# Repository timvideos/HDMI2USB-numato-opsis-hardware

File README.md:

The <a href="http://hdmi2usb.tv/numato-opsis">Numato Opsis</a>, the first open hardware for the
<a href="http://hdmi2usb.tv">HDMI2USB firmware</a>,
<a href="https://numato.com/product/numato-opsis-fpga-based-open-video-platform">can now be ordered
From Numato Labs
</a>

## Opsis Board - A open source HDMI2USB board

The [Numato](http://numato.com) Opsis board is the first
[HDMI2USB](http://hdmi2usb.tv) production board developed in conjugation with
the [TimVideos.us](http://code.timvideos.us) project. 

It's features include;
 * 2 x HDMI input ports,
 * 2 x HDMI output ports,
 * DisplayPort input and output ports,
 * 128Mbit DDR3-1600 ram,
 * Gigabit Ethernet with MAC address EEPROM,
 * Micro SD card,
 * Cypress FX2 for USB device functionality,
 * ULPI for USB OTG functionality,
 * Quad speed SPI flash.

Sample code for the Opsis can be found at https://github.com/timvideos/HDMI2USB-numato-opsis-sample-code

## Editing

The design in this repository was made using [KiCad](http://www.kicad-pcb.org/)
version **2013-07-07 BZR 4022**
([the version in Ubuntu Trusty](http://packages.ubuntu.com/trusty/kicad)).

## License

Opsis Board by Numato Systems Pvt. Ltd

The Numato HDMI2USB board is licensed under a
Creative Commons Attribution-ShareAlike 4.0 International License.

You should have received a copy of the license along with this
work. If not, see <http://creativecommons.org/licenses/by-sa/4.0/>.

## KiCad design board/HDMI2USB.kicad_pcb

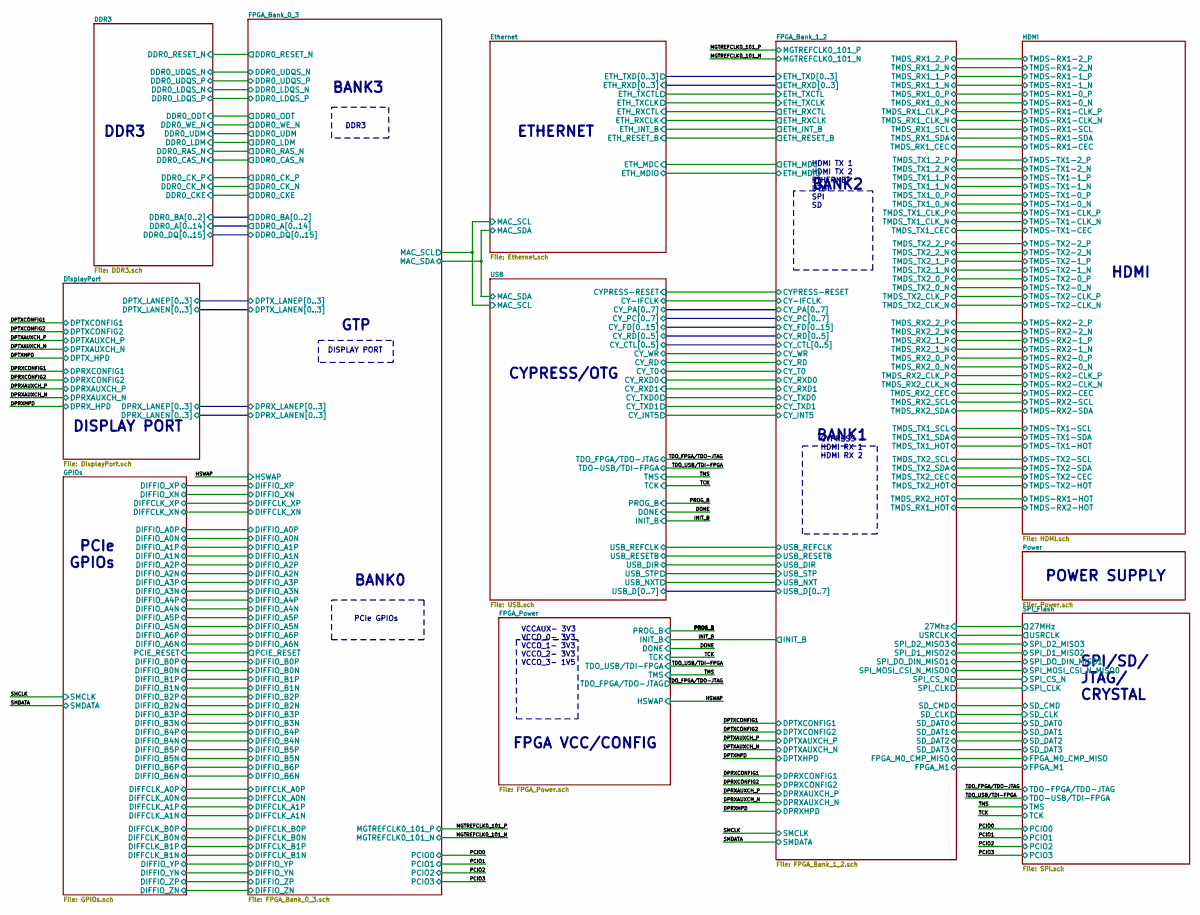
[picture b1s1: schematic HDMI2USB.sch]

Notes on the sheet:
HDMI
POWER SUPPLY
SPI/SD/ JTAG/ CRYSTAL
DISPLAY PORT
PCIe GPIOs
ETHERNET
CYPRESS/OTG
FPGA VCC/CONFIG
DDR3
BANK0
BANK3
BANK2
BANK1
PCIe GPIOs
GTP
CYPRESS HDMI RX 1 HDMI RX 2
HDMI TX 1 HDMI TX 2 ETHERNET UTMI SPI SD
VCCAUX- 3V3 VCCO_0- 3V3 VCCO_1- 3V3 VCCO_2- 3V3 VCCO_3- 1V5

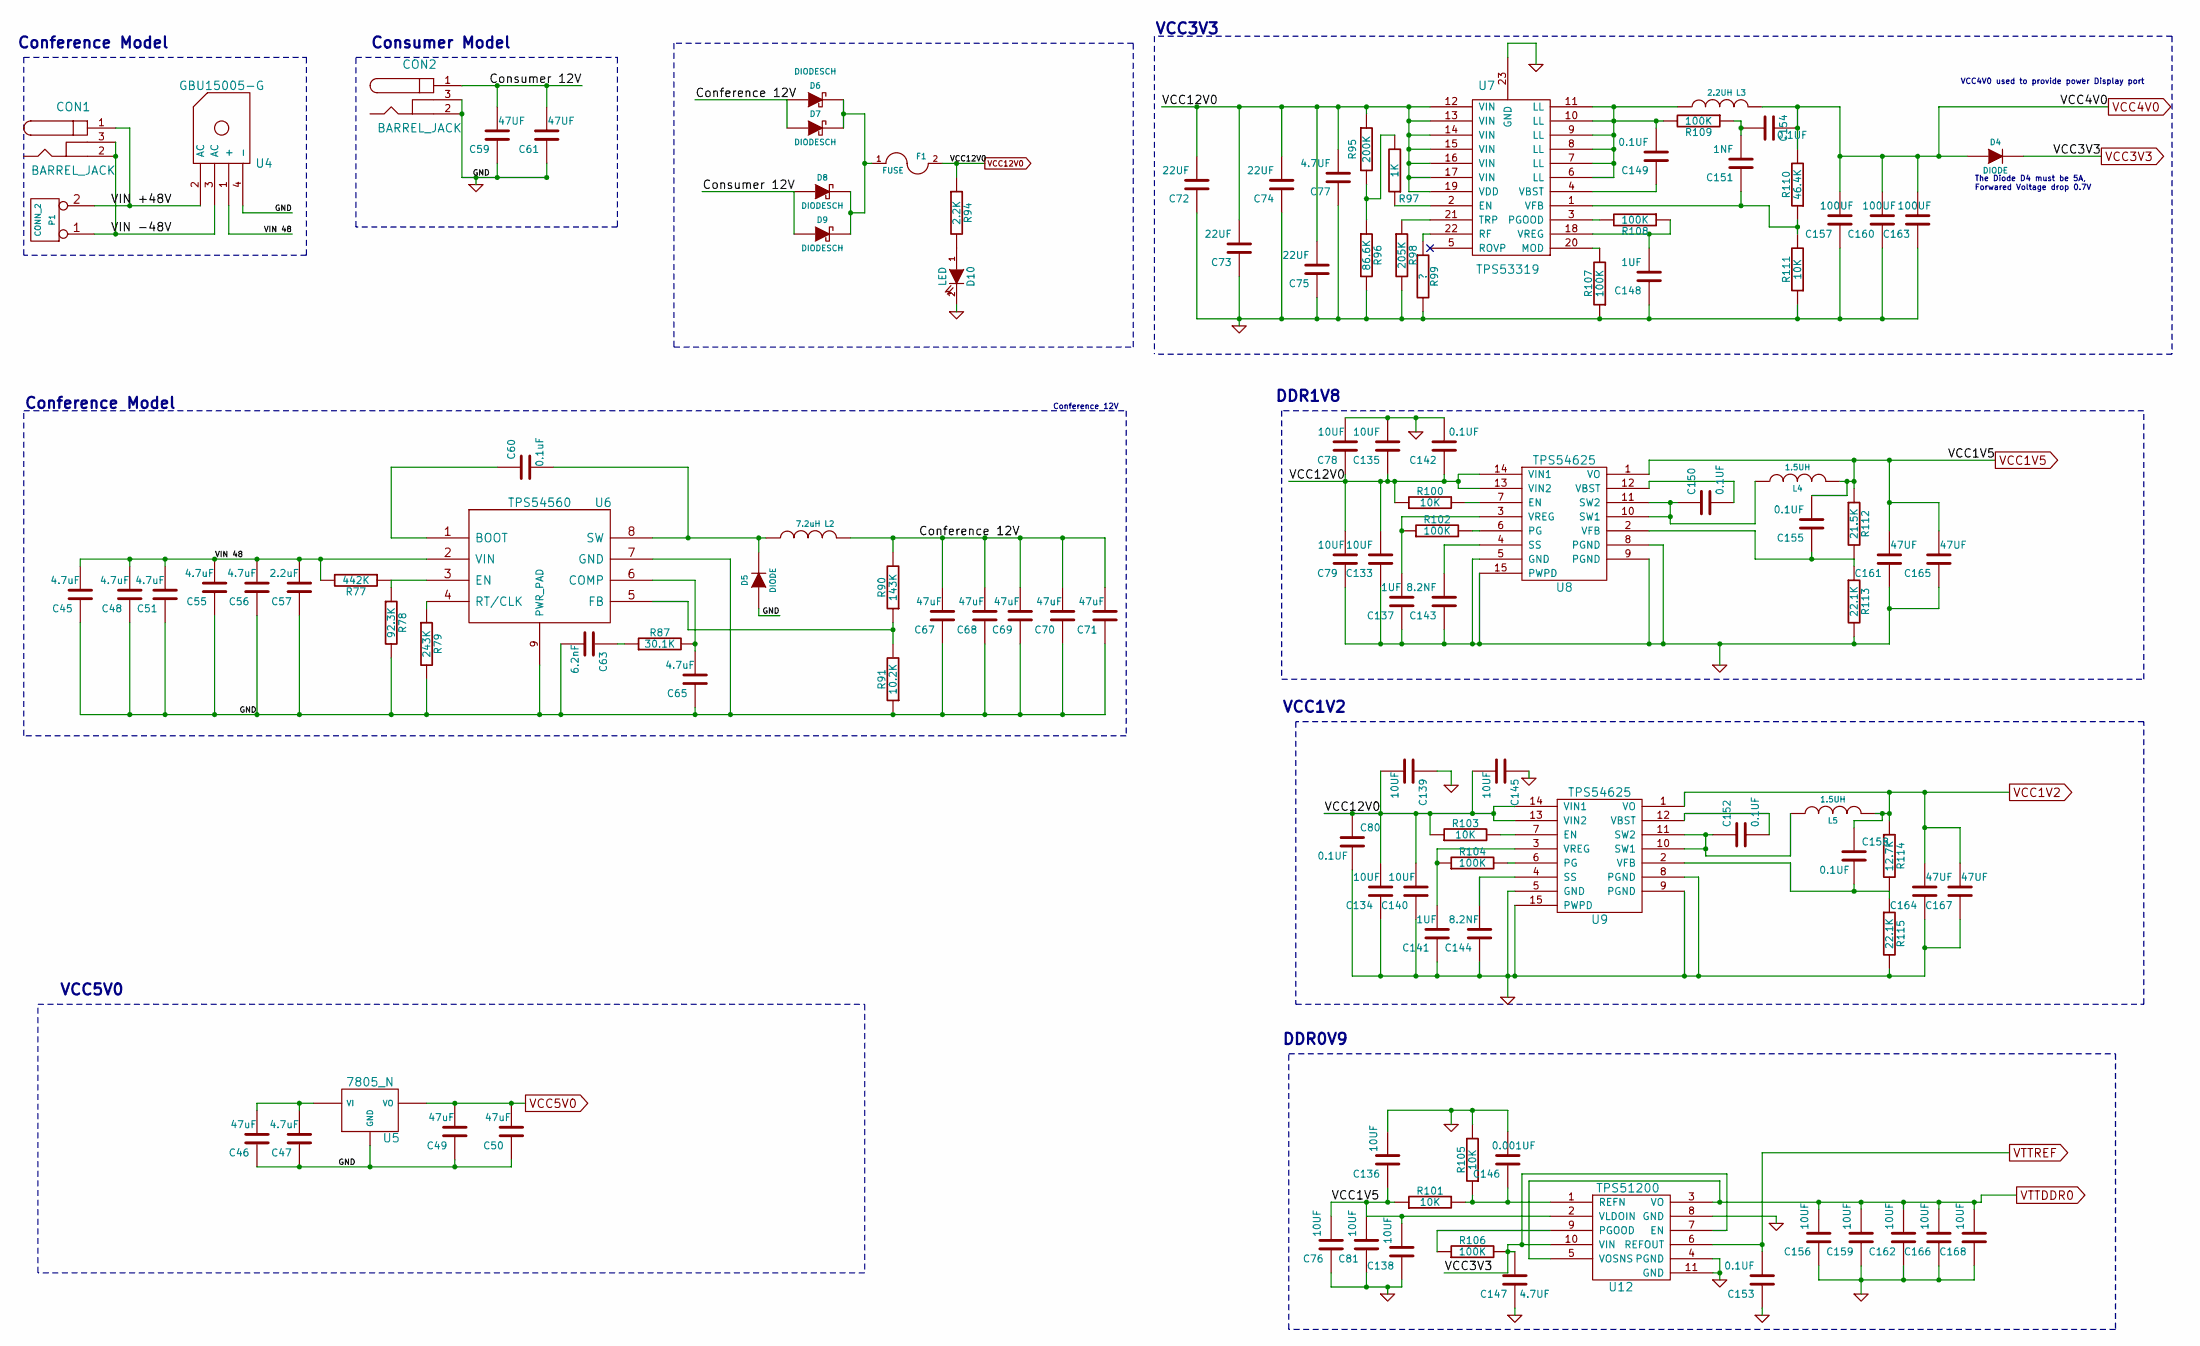
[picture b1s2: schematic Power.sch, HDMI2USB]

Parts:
C45, C47, C48, C51, C55, C56, C65: 4.7uF
C46, C49, C50, C67, C68, C69, C70, C71: 47uF
C57: 2.2uF
C59, C61, C161, C164, C165, C167: 47UF
C60: 0.1uF
C63: 6.2nF
C72, C73, C74, C75: 22UF
C76, C78, C79, C81, C133, C134, C135, C136, C138, C139, C140, C145, C156, C159, C162, C166, C168: 10UF
C77, C147: 4.7UF
C80, C142, C149, C150, C152, C153, C154, C155, C158: 0.1UF
C137, C141, C148: 1UF
C143, C144: 8.2NF
C146: 0.001UF
C151: 1NF
C157, C160, C163: 100UF
CON1, CON2: BARREL_JACK
D4, D5: DIODE
D6, D7, D8, D9: DIODESCH
D10: LED
F1: FUSE
L2: 7.2uH
L3: 2.2UH
L4, L5: 1.5UH
P1: CONN_2
R77: 442K
R78: 92.3K
R79: 243K
R87: 30.1K
R90: 143K
R91: 10.2K
R94: 2.2K
R95: 200K
R96: 86.6K
R97: 1K
R98: 205K
R99: ?
R100, R101, R103, R105, R111: 10K
R102, R104, R106, R107, R108, R109: 100K
R110: 46.4K
R112: 21.5K
R113, R115: 22.1K
R114: 12.7K
U4: GBU15005-G
U5: 7805_N
U6: TPS54560
U7: TPS53319
U8, U9: TPS54625
U12: TPS51200

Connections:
/Power/Conference 12V: C67.2, C68.2, C69.2, C70.2, C71.2, D6.1 (A), D7.1 (A), L2.2, R90.2
/Power/Consumer 12V: C59.2, C61.2, CON2.1, D8.1 (A), D9.1 (A)
/Power/VIN 48: C45.2, C48.2, C51.2, C55.2, C56.2, C57.2, R77.2, U4.1 (+), U6.2 (VIN)
/Power/VIN +48V: CON1.1, P1.2 (PM), U4.2 (AC)
/Power/VIN -48V: CON1.2, CON1.3, P1.1, U4.3 (AC)
unnamed: C65.2, R87.2, U6.6 (COMP)
unnamed: C63.1, R87.1
unnamed: C150.2, U8.12 (VBST)
unnamed: C150.1, L4.1, U8.10 (SW1), U8.11 (SW2)
unnamed: R79.1, U6.4 (RT/CLK)
unnamed: R77.1, R78.1, U6.3 (EN)
unnamed: C60.1, U6.1 (BOOT)
unnamed: C144.2, U9.4 (SS)
unnamed: R104.2, U9.6 (PG)
unnamed: C152.2, U9.12 (VBST)
unnamed: R103.2, U9.7 (EN)
unnamed: R102.2, U8.6 (PG)
unnamed: C143.2, U8.4 (SS)
unnamed: C152.1, L5.1, U9.10 (SW1), U9.11 (SW2)
unnamed: R100.2, U8.7 (EN)
unnamed: C149.1, U7.4 (VBST)
unnamed: C141.2, R104.1, U9.3 (VREG)
unnamed: R108.2, U7.3 (PGOOD)
unnamed: C148.2, R108.1, U7.18 (VREG)
unnamed: R107.2, U7.20 (MOD)
unnamed: R99.1, U7.22 (RF)
unnamed: R98.1, U7.21 (TRP)
unnamed: C137.2, R102.1, U8.3 (VREG)
unnamed: R97.1, U7.2 (EN)
unnamed: R106.1, U12.9 (PGOOD)
unnamed: R90.1, R91.2, U6.5 (FB)
unnamed: C60.2, D5.2 (K), L2.1, U6.8 (SW)
unnamed: C153.2, U12.6 (REFOUT)
unnamed: C158.2, R114.2, R115.1, U9.2 (VFB)
unnamed: C155.1, R112.2, R113.1, U8.2 (VFB)
unnamed: C46.2, C47.2, U5.1 (VI)
unnamed: D6.2 (K), D7.2 (K), D8.2 (K), D9.2 (K), F1.1
unnamed: C146.1, R101.2, R105.1, U12.1 (REFN)
unnamed: C151.1, R110.1, R111.2, U7.1 (VFB)
unnamed: C149.2, L3.1, R109.2, U7.6 (LL), U7.7 (LL), U7.8 (LL), U7.9 (LL), U7.10 (LL), U7.11 (LL)
unnamed: R95.2, R96.1, R97.2
unnamed: D10.1 (A), R94.2
VCC1V2: C158.1, C164.2, C167.2, L5.2, R114.1, U9.1 (VO); also elsewhere on the board
VCC1V5: C76.2, C81.2, C136.1, C138.2, C155.2, C161.2, C165.2, L4.2, R101.1, R112.1, U8.1 (VO), U12.2 (VLDOIN); also elsewhere on the board
VCC5V0: C49.2, C50.2, U5.3 (VO); also elsewhere on the board
VCC12V0: C72.2, C73.2, C74.2, C75.2, C77.2, C78.1, C79.2, C80.1, C133.2, C134.2, C135.1, C139.2, C140.2, C142.1, C145.2, F1.2, R94.1, R95.1, R100.1, R103.1, U7.12 (VIN), U7.13 (VIN), U7.14 (VIN), U7.15 (VIN), U7.16 (VIN), U7.17 (VIN), U7.19 (VDD), U8.13 (VIN2), U8.14 (VIN1), U9.13 (VIN2), U9.14 (VIN1); also elsewhere on the board
VTTDDR0: C156.2, C159.2, C162.2, C166.2, C168.2, U12.3 (VO), U12.5 (VOSNS); also elsewhere on the board

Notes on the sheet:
VCC3V3
DDR1V8
VCC1V2
DDR0V9
Consumer Model
Conference Model
Conference 12V
VCC5V0
VCC4V0 used to provide power Display port
The Diode D4 must be 5A, Forwared Voltage drop 0.7V

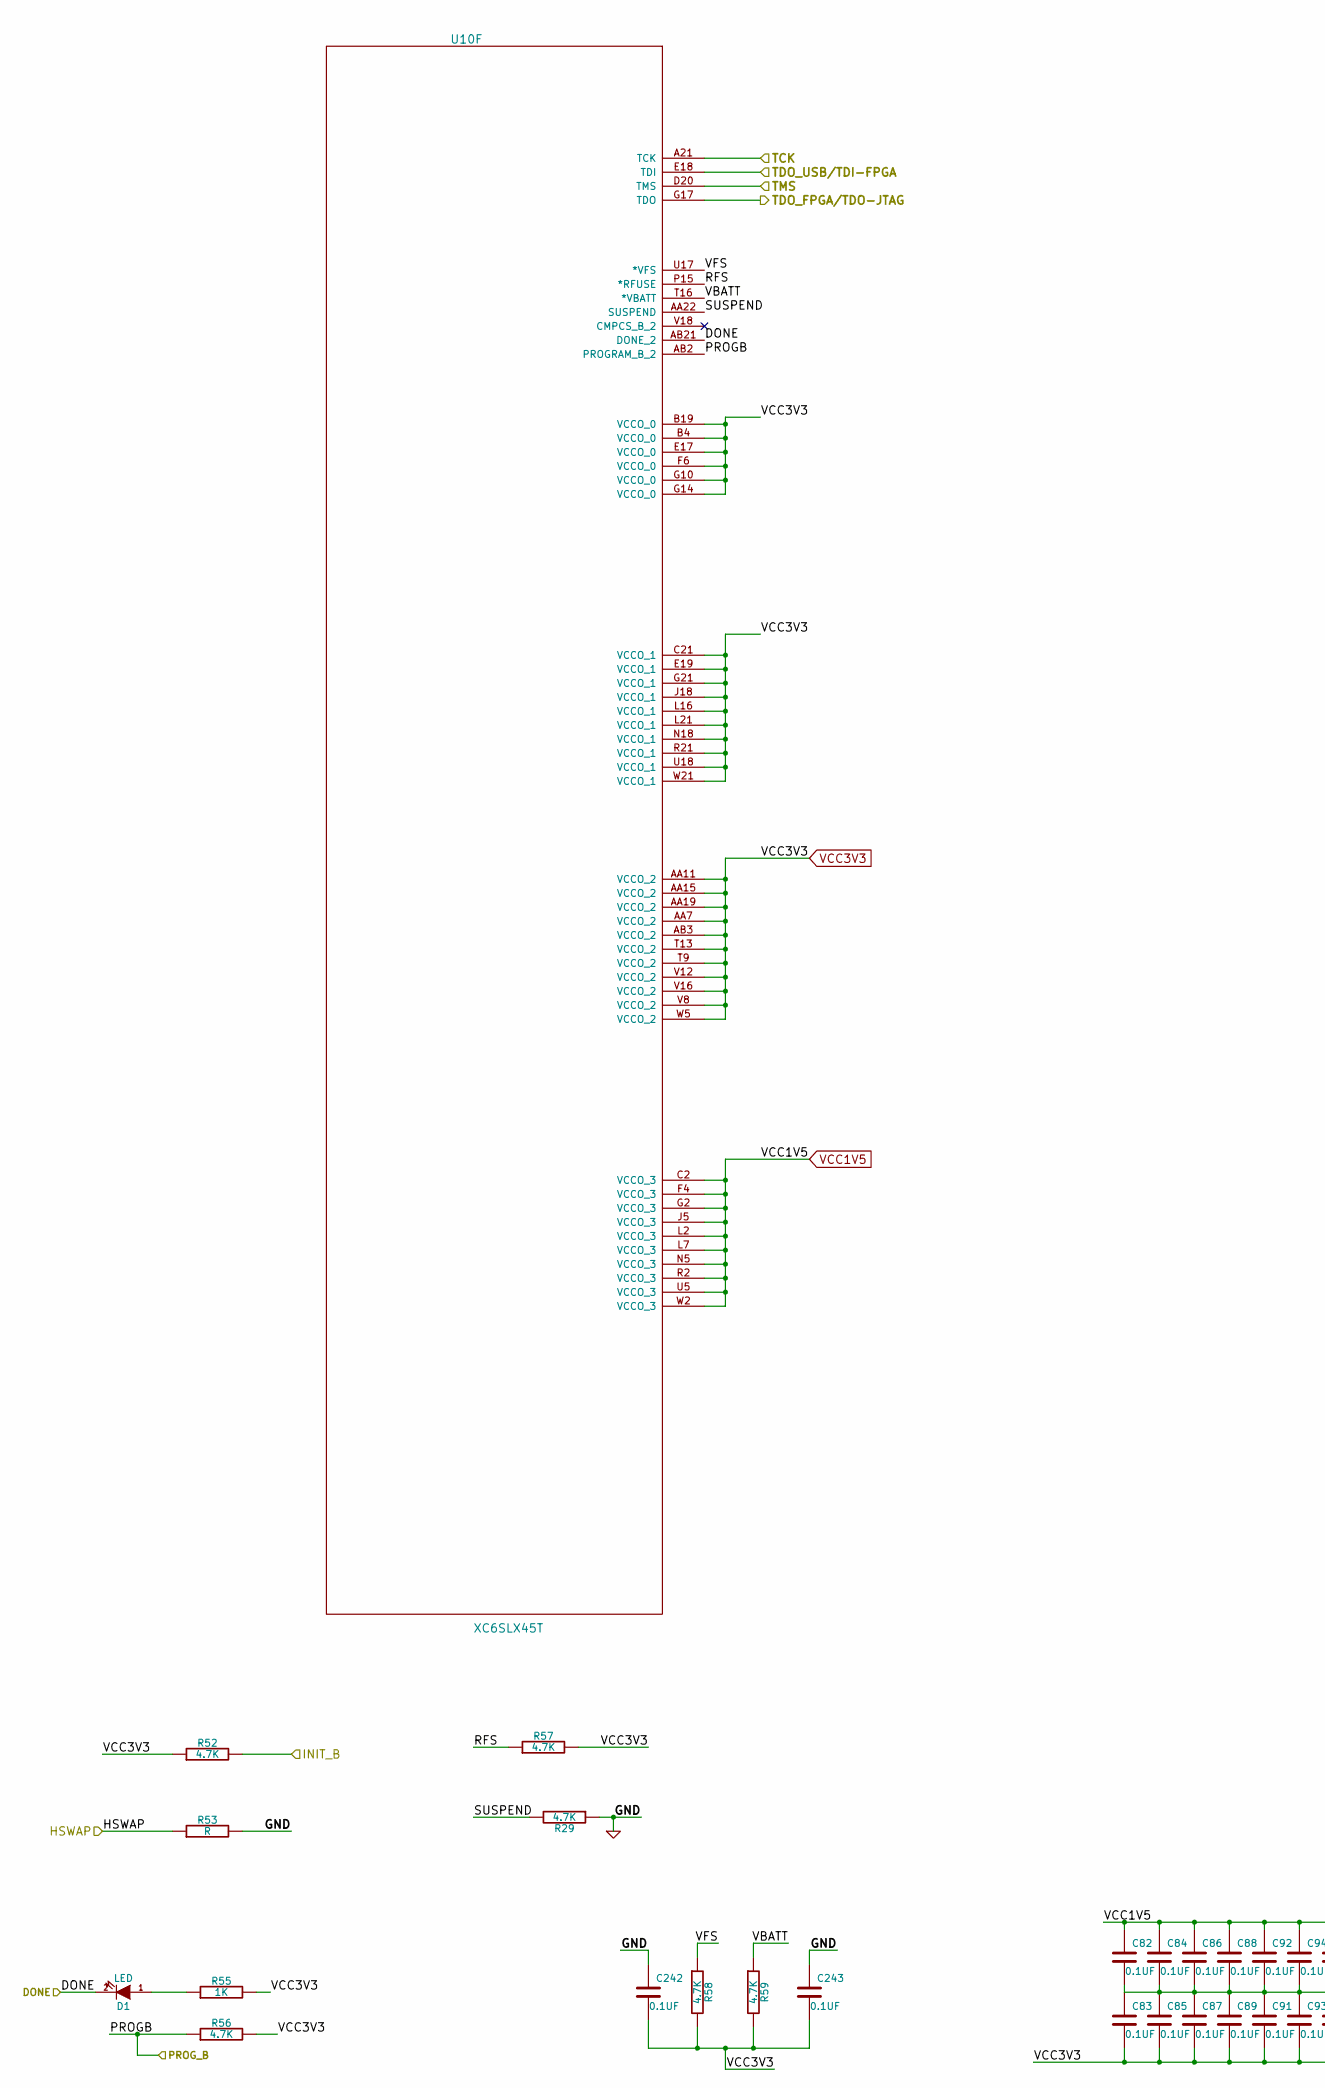
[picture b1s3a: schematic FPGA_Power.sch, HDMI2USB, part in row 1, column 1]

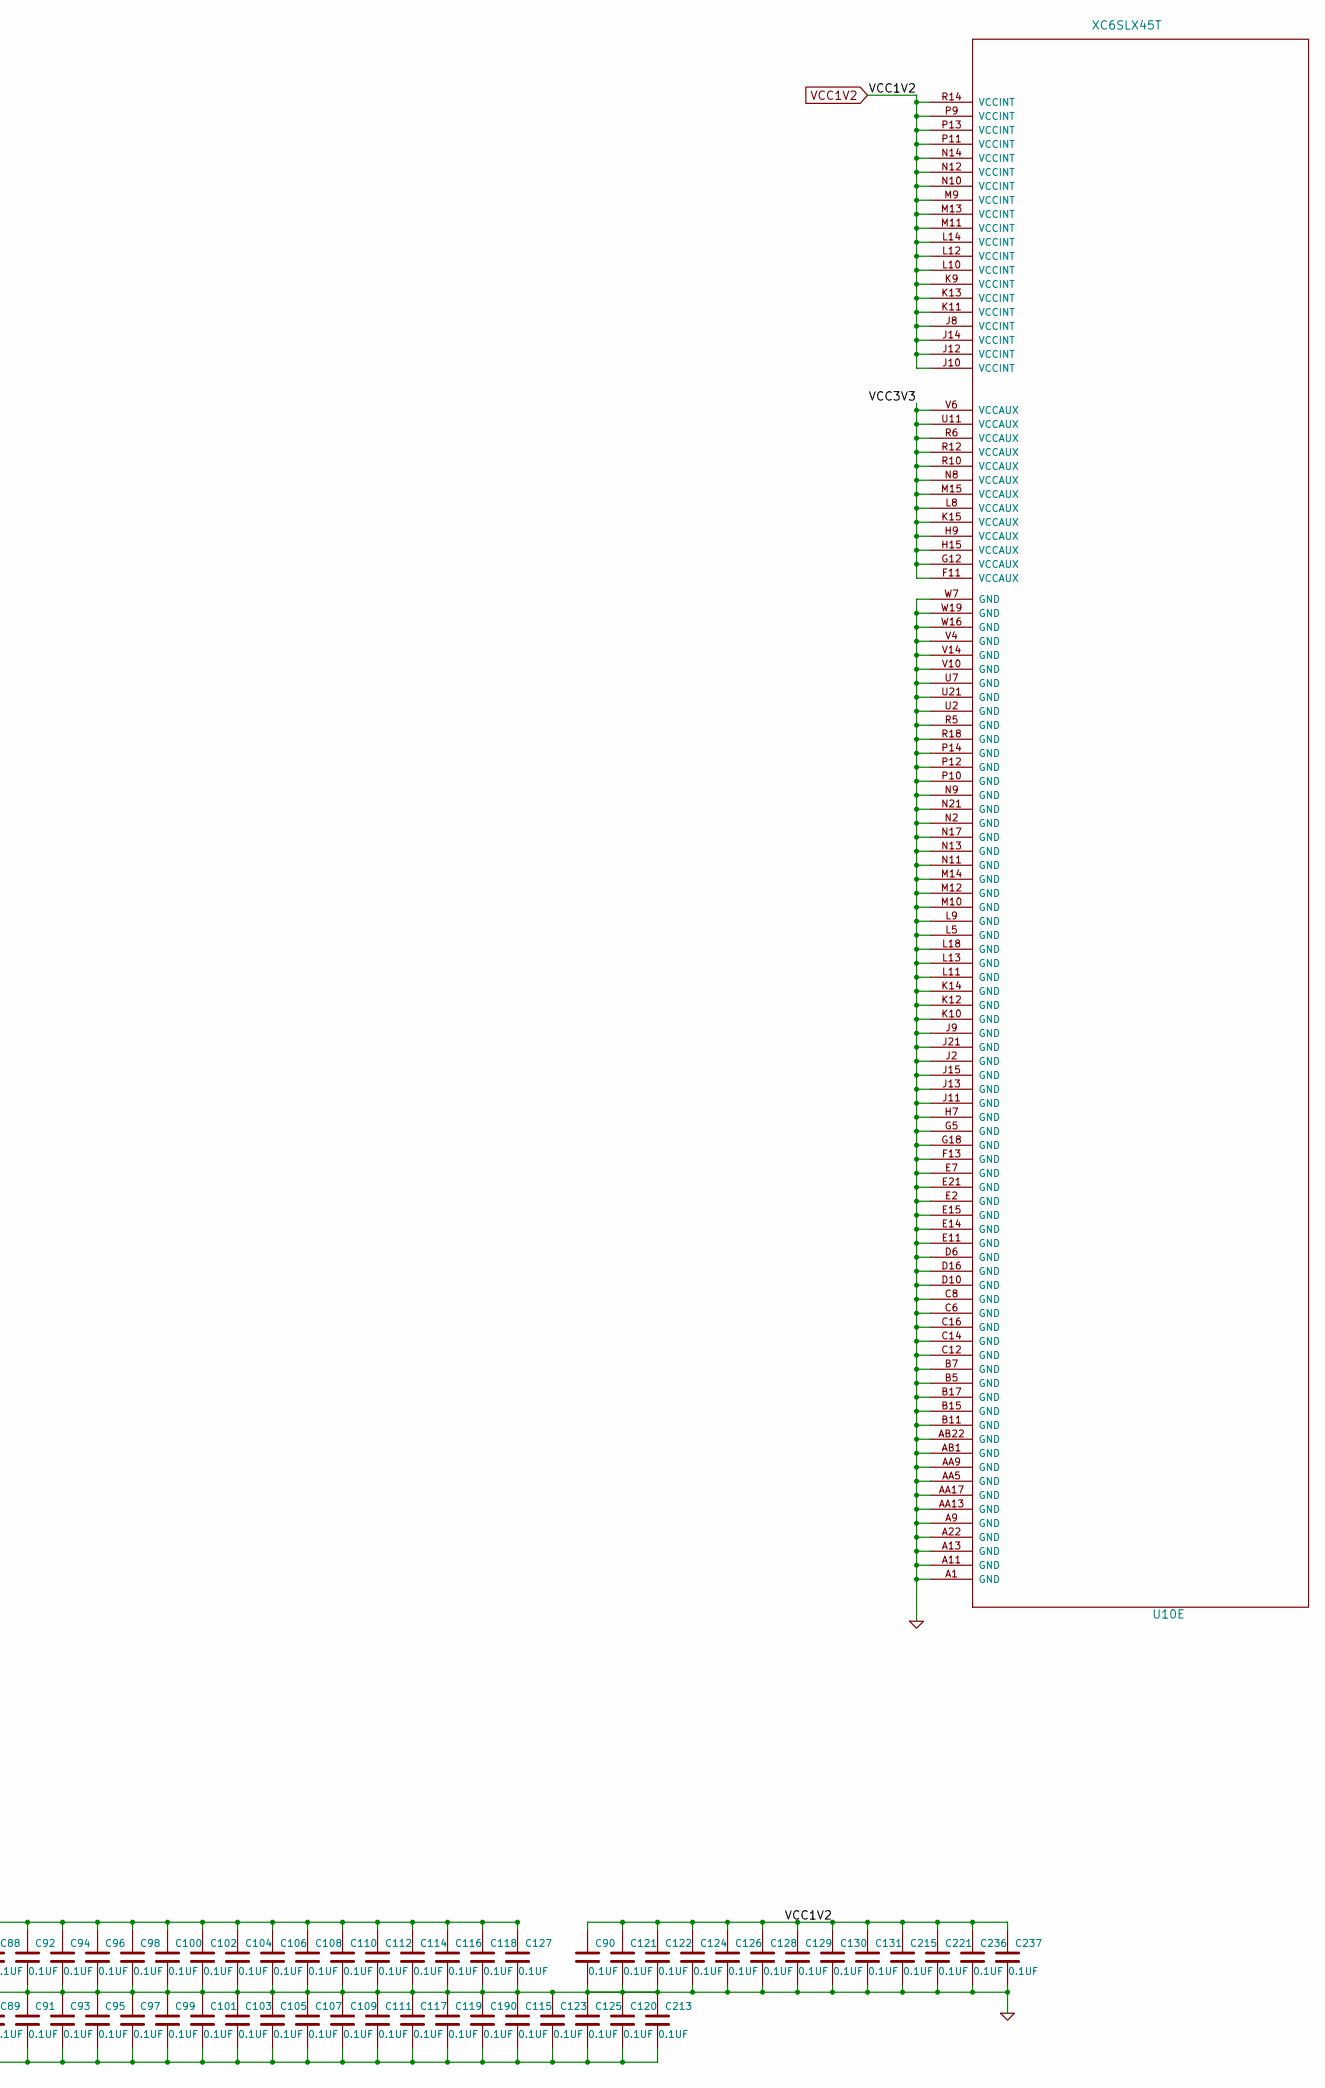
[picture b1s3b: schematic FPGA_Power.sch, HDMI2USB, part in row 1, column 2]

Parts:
C82, C83, C84, C85, C86, C87, C88, C89, C90, C91, C92, C93, C94, C95, C96, C97, C98, C99, C100, C101, C102, C103, C104, C105, C106, C107, C108, C109, C110, C111, C112, C114, C115, C116, C117, C118, C119, C120, C121, C122, C123, C124, C125, C126, C127, C128, C129, C130, C131, C190, C213, C215, C221, C236, C237, C242, C243: 0.1UF
D1: LED
R29, R52, R56, R57: 4.7K
R53: R
R55: 1K
R58, R59: 4.7K
U10: XC6SLX45T

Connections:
/FPGA_Bank_0_3/HSWAP: R53.1; also elsewhere on the board
/FPGA_Bank_1_2/INIT_B: R52.2; also elsewhere on the board
/FPGA_Power/DONE: D1.2 (K), U10.AB21 (DONE_2); also elsewhere on the board
/FPGA_Power/PROG_B: R56.1, U10.AB2 (PROGRAM_B_2); also elsewhere on the board
/FPGA_Power/RFS: R57.1, U10.P15 (*RFUSE)
/FPGA_Power/SUSPEND: R29.2, U10.AA22 (SUSPEND)
/FPGA_Power/TCK: U10.A21 (TCK); also elsewhere on the board
/FPGA_Power/TMS: U10.D20 (TMS); also elsewhere on the board
/FPGA_Power/VBATT: R59.1, U10.T16 (*VBATT)
/FPGA_Power/VFS: R58.1, U10.U17 (*VFS)
/SPI_Flash/TDO-FPGA/TDO-JTAG: U10.G17 (TDO); also elsewhere on the board
/SPI_Flash/TDO-USB/TDI-FPGA: U10.E18 (TDI); also elsewhere on the board
unnamed: D1.1 (A), R55.1
VCC1V2: C90.1, C121.1, C122.1, C124.1, C126.1, C128.1, C129.1, C130.1, C131.1, C215.1, C221.1, C236.1, C237.1, U10.J8 (VCCINT), U10.J10 (VCCINT), U10.J12 (VCCINT), U10.J14 (VCCINT), U10.K9 (VCCINT), U10.K11 (VCCINT), U10.K13 (VCCINT), U10.L10 (VCCINT), U10.L12 (VCCINT), U10.L14 (VCCINT), U10.M9 (VCCINT), U10.M11 (VCCINT), U10.M13 (VCCINT), U10.N10 (VCCINT), U10.N12 (VCCINT), U10.N14 (VCCINT), U10.P9 (VCCINT), U10.P11 (VCCINT), U10.P13 (VCCINT), U10.R14 (VCCINT); also elsewhere on the board
VCC1V5: C82.1, C84.1, C86.1, C88.1, C92.1, C94.1, C96.1, C98.1, C100.1, C102.1, C104.1, C106.1, C108.1, C110.1, C112.1, C114.1, C116.1, C118.1, C127.1, U10.C2 (VCCO_3), U10.F4 (VCCO_3), U10.G2 (VCCO_3), U10.J5 (VCCO_3), U10.L2 (VCCO_3), U10.L7 (VCCO_3), U10.N5 (VCCO_3), U10.R2 (VCCO_3), U10.U5 (VCCO_3), U10.W2 (VCCO_3); also elsewhere on the board

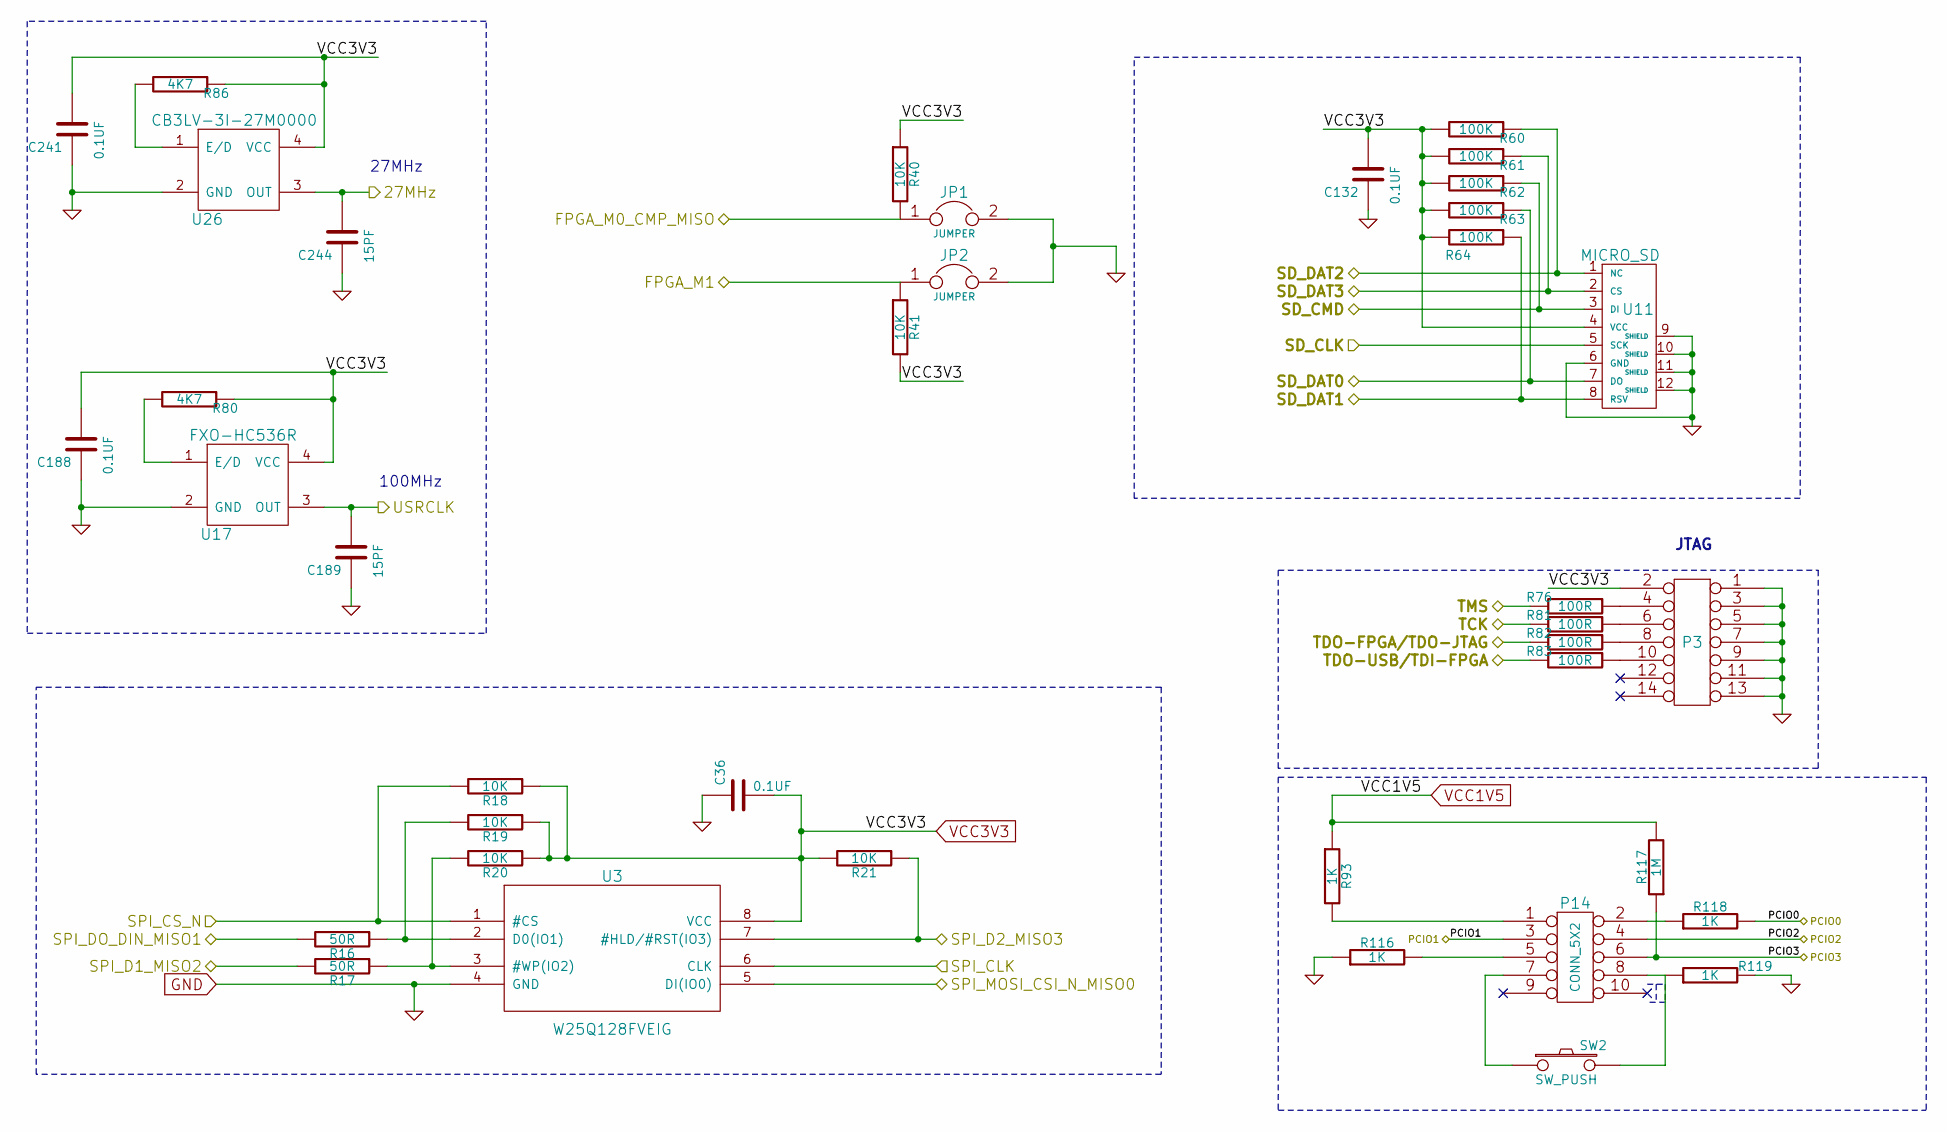
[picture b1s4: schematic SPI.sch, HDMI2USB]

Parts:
C36, C132, C188, C241: 0.1UF
C189, C244: 15PF
JP1, JP2: JUMPER
P3: CONN_7X2
P14: CONN_5X2
R16, R17: 50R
R18, R19, R20, R21, R40, R41: 10K
R60, R61, R62, R63, R64: 100K
R76, R81, R82, R83: 100R
R80, R86: 4K7
R93, R116, R118, R119: 1K
R117: 1M
SW2: SW_PUSH
U3: W25Q128FVEIG
U11: MICRO_SD
U17: FXO-HC536R
U26: CB3LV-3I-27M0000

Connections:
/Ethernet/MAC_SDA: R93.1, R117.2; also elsewhere on the board
/Ethernet/VCC3V3: P14.1, P14.5, R93.2, R116.2; also elsewhere on the board
/Ethernet/XTAL1_50MHZ: R86.2, U26.1 (E/D); also elsewhere on the board
/FPGA_Bank_1_2/FPGA_M0_CMP_MISO: JP1.1, R40.2; also elsewhere on the board
/FPGA_Bank_1_2/FPGA_M1: JP2.1, R41.1; also elsewhere on the board
/FPGA_Bank_1_2/SD_CLK: U11.5 (SCK); also elsewhere on the board
/FPGA_Bank_1_2/SD_CMD: R62.1, U11.3 (DI); also elsewhere on the board
/FPGA_Bank_1_2/SD_DAT0: R63.1, U11.7 (DO); also elsewhere on the board
/FPGA_Bank_1_2/SD_DAT1: R64.1, U11.8 (RSV); also elsewhere on the board
/FPGA_Bank_1_2/SD_DAT2: R60.1, U11.1 (NC); also elsewhere on the board
/FPGA_Bank_1_2/SD_DAT3: R61.1, U11.2 (CS); also elsewhere on the board
/FPGA_Bank_1_2/SPI_CLK: U3.6 (CLK); also elsewhere on the board
/FPGA_Bank_1_2/SPI_CS_N: R18.2, U3.1 (#CS); also elsewhere on the board
/FPGA_Bank_1_2/SPI_D1_MISO2: R17.2; also elsewhere on the board
/FPGA_Bank_1_2/SPI_D2_MISO3: R21.1, U3.7 (#HLD/#RST(IO3)); also elsewhere on the board
/FPGA_Bank_1_2/SPI_DO_DIN_MISO1: R16.2; also elsewhere on the board
/FPGA_Bank_1_2/SPI_MOSI_CSI_N_MISO0: U3.5 (DI(IO0)); also elsewhere on the board
/FPGA_Bank_1_2/USRCLK: C189.2, U17.3 (OUT); also elsewhere on the board
/FPGA_Power/TCK: R81.2; also elsewhere on the board
/FPGA_Power/TMS: R76.2; also elsewhere on the board
/SPI_Flash/TDO-FPGA/TDO-JTAG: R82.2; also elsewhere on the board
/SPI_Flash/TDO-USB/TDI-FPGA: R83.2; also elsewhere on the board
unnamed: R16.1, R19.2, U3.2 (D0(IO1))
unnamed: R17.1, R20.2, U3.3 (#WP(IO2))
unnamed: P3.4, R76.1
unnamed: P3.6, R81.1
unnamed: P3.8, R82.1
unnamed: P3.10, R83.1
unnamed: R80.2, U17.1 (E/D)
unnamed: C244.2, U26.3 (OUT)
unnamed: P14.2, R118.1
unnamed: P14.6, R117.1
unnamed: P14.7, SW2.1
unnamed: P14.8, R119.1, SW2.2

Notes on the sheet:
JTAG
100MHz
27MHz

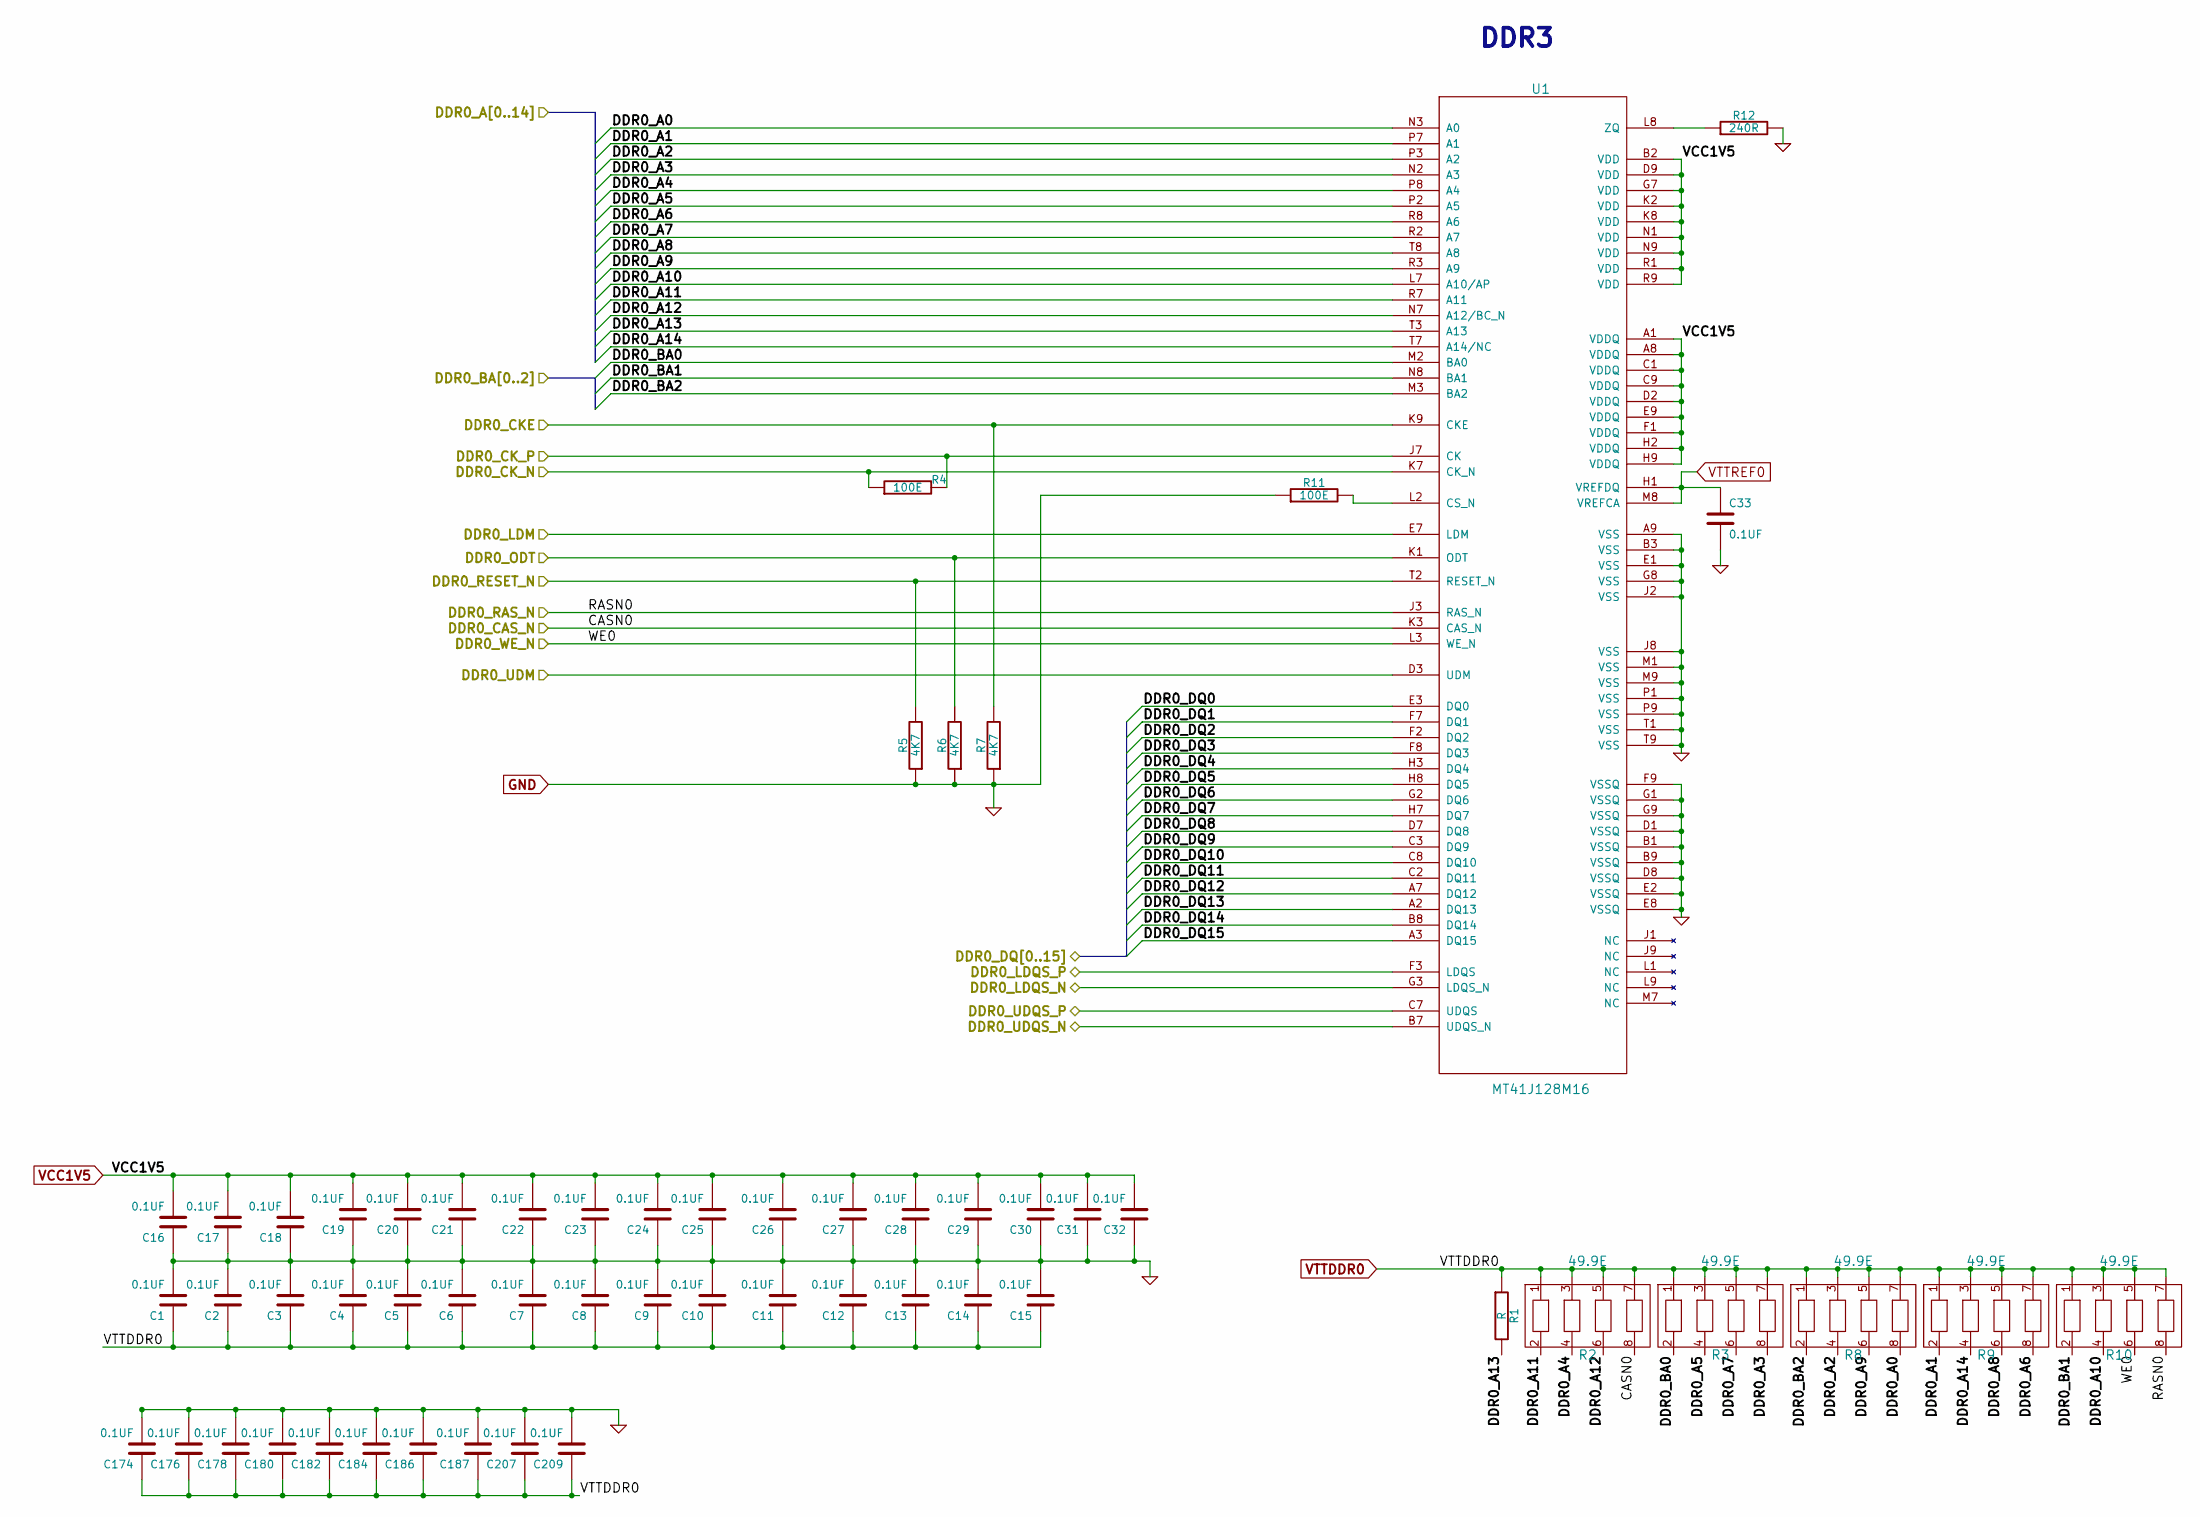
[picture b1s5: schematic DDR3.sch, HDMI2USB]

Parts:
C1, C2, C3, C4, C5, C6, C7, C8, C9, C10, C11, C12, C13, C14, C15, C16, C17, C18, C19, C20, C21, C22, C23, C24, C25, C26, C27, C28, C29, C30, C31, C32, C33, C174, C176, C178, C180, C182, C184, C186, C187, C207, C209: 0.1UF
R1: R
R2, R3, R8, R9, R10: 49.9E
R4, R11: 100E
R5, R6, R7: 4K7
R12: 240R
U1: MT41J128M16

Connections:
/DDR3/DDR0_A0: R8.8, U1.N3 (A0); also elsewhere on the board
/DDR3/DDR0_A1: R9.2, U1.P7 (A1); also elsewhere on the board
/DDR3/DDR0_A2: R8.4, U1.P3 (A2); also elsewhere on the board
/DDR3/DDR0_A3: R3.8, U1.N2 (A3); also elsewhere on the board
/DDR3/DDR0_A4: R2.4, U1.P8 (A4); also elsewhere on the board
/DDR3/DDR0_A5: R3.4, U1.P2 (A5); also elsewhere on the board
/DDR3/DDR0_A6: R9.8, U1.R8 (A6); also elsewhere on the board
/DDR3/DDR0_A7: R3.6, U1.R2 (A7); also elsewhere on the board
/DDR3/DDR0_A8: R9.6, U1.T8 (A8); also elsewhere on the board
/DDR3/DDR0_A9: R8.6, U1.R3 (A9); also elsewhere on the board
/DDR3/DDR0_A10: R10.4, U1.L7 (A10/AP); also elsewhere on the board
/DDR3/DDR0_A11: R2.2, U1.R7 (A11); also elsewhere on the board
/DDR3/DDR0_A12: R2.6, U1.N7 (A12/BC_N); also elsewhere on the board
/DDR3/DDR0_A13: R1.2, U1.T3 (A13); also elsewhere on the board
/DDR3/DDR0_A14: R9.4, U1.T7 (A14/NC); also elsewhere on the board
/DDR3/DDR0_BA0: R3.2, U1.M2 (BA0); also elsewhere on the board
/DDR3/DDR0_BA1: R10.2, U1.N8 (BA1); also elsewhere on the board
/DDR3/DDR0_BA2: R8.2, U1.M3 (BA2); also elsewhere on the board
/DDR3/DDR0_CAS_N: R2.8, U1.K3 (CAS_N); also elsewhere on the board
/DDR3/DDR0_CKE: R7.2, U1.K9 (CKE); also elsewhere on the board
/DDR3/DDR0_CK_N: R4.1, U1.K7 (CK_N); also elsewhere on the board
/DDR3/DDR0_CK_P: R4.2, U1.J7 (CK); also elsewhere on the board
/DDR3/DDR0_DQ0: U1.E3 (DQ0); also elsewhere on the board
/DDR3/DDR0_DQ1: U1.F7 (DQ1); also elsewhere on the board
/DDR3/DDR0_DQ2: U1.F2 (DQ2); also elsewhere on the board
/DDR3/DDR0_DQ3: U1.F8 (DQ3); also elsewhere on the board
/DDR3/DDR0_DQ4: U1.H3 (DQ4); also elsewhere on the board
/DDR3/DDR0_DQ5: U1.H8 (DQ5); also elsewhere on the board
/DDR3/DDR0_DQ6: U1.G2 (DQ6); also elsewhere on the board
/DDR3/DDR0_DQ7: U1.H7 (DQ7); also elsewhere on the board
/DDR3/DDR0_DQ8: U1.D7 (DQ8); also elsewhere on the board
/DDR3/DDR0_DQ9: U1.C3 (DQ9); also elsewhere on the board
/DDR3/DDR0_DQ10: U1.C8 (DQ10); also elsewhere on the board
/DDR3/DDR0_DQ11: U1.C2 (DQ11); also elsewhere on the board
/DDR3/DDR0_DQ12: U1.A7 (DQ12); also elsewhere on the board
/DDR3/DDR0_DQ13: U1.A2 (DQ13); also elsewhere on the board
/DDR3/DDR0_DQ14: U1.B8 (DQ14); also elsewhere on the board
/DDR3/DDR0_DQ15: U1.A3 (DQ15); also elsewhere on the board
/DDR3/DDR0_LDM: U1.E7 (LDM); also elsewhere on the board
/DDR3/DDR0_LDQS_N: U1.G3 (LDQS_N); also elsewhere on the board
/DDR3/DDR0_LDQS_P: U1.F3 (LDQS); also elsewhere on the board
/DDR3/DDR0_ODT: R6.2, U1.K1 (ODT); also elsewhere on the board
/DDR3/DDR0_RAS_N: R10.8, U1.J3 (RAS_N); also elsewhere on the board
/DDR3/DDR0_RESET_N: R5.2, U1.T2 (RESET_N); also elsewhere on the board
/DDR3/DDR0_UDM: U1.D3 (UDM); also elsewhere on the board
/DDR3/DDR0_UDQS_N: U1.B7 (UDQS_N); also elsewhere on the board
/DDR3/DDR0_UDQS_P: U1.C7 (UDQS); also elsewhere on the board
/DDR3/DDR0_WE_N: R10.6, U1.L3 (WE_N); also elsewhere on the board
unnamed: R11.2, U1.L2 (CS_N)
unnamed: R12.1, U1.L8 (ZQ)
VCC1V5: C16.2, C17.2, C18.2, C19.2, C20.2, C21.2, C22.2, C23.2, C24.2, C25.2, C26.2, C27.2, C28.2, C29.2, C30.2, C31.2, C32.2, U1.A1 (VDDQ), U1.A8 (VDDQ), U1.B2 (VDD), U1.C1 (VDDQ), U1.C9 (VDDQ), U1.D2 (VDDQ), U1.D9 (VDD), U1.E9 (VDDQ), U1.F1 (VDDQ), U1.G7 (VDD), U1.H2 (VDDQ), U1.H9 (VDDQ), U1.K2 (VDD), U1.K8 (VDD), U1.N1 (VDD), U1.N9 (VDD), U1.R1 (VDD), U1.R9 (VDD); also elsewhere on the board
VTTDDR0: C1.1, C2.1, C3.1, C4.1, C5.1, C6.1, C7.1, C8.1, C9.1, C10.1, C11.1, C12.1, C13.1, C14.1, C15.1, C174.1, C176.1, C178.1, C180.1, C182.1, C184.1, C186.1, C187.1, C207.1, C209.1, R1.1, R2.1, R2.3, R2.5, R2.7, R3.1, R3.3, R3.5, R3.7, R8.1, R8.3, R8.5, R8.7, R9.1, R9.3, R9.5, R9.7, R10.1, R10.3, R10.5, R10.7; also elsewhere on the board
VTTREF0: C33.1, U1.H1 (VREFDQ), U1.M8 (VREFCA); also elsewhere on the board

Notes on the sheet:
DDR3

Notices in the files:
board/Ethernet.sch:
License: CC BY-SA
